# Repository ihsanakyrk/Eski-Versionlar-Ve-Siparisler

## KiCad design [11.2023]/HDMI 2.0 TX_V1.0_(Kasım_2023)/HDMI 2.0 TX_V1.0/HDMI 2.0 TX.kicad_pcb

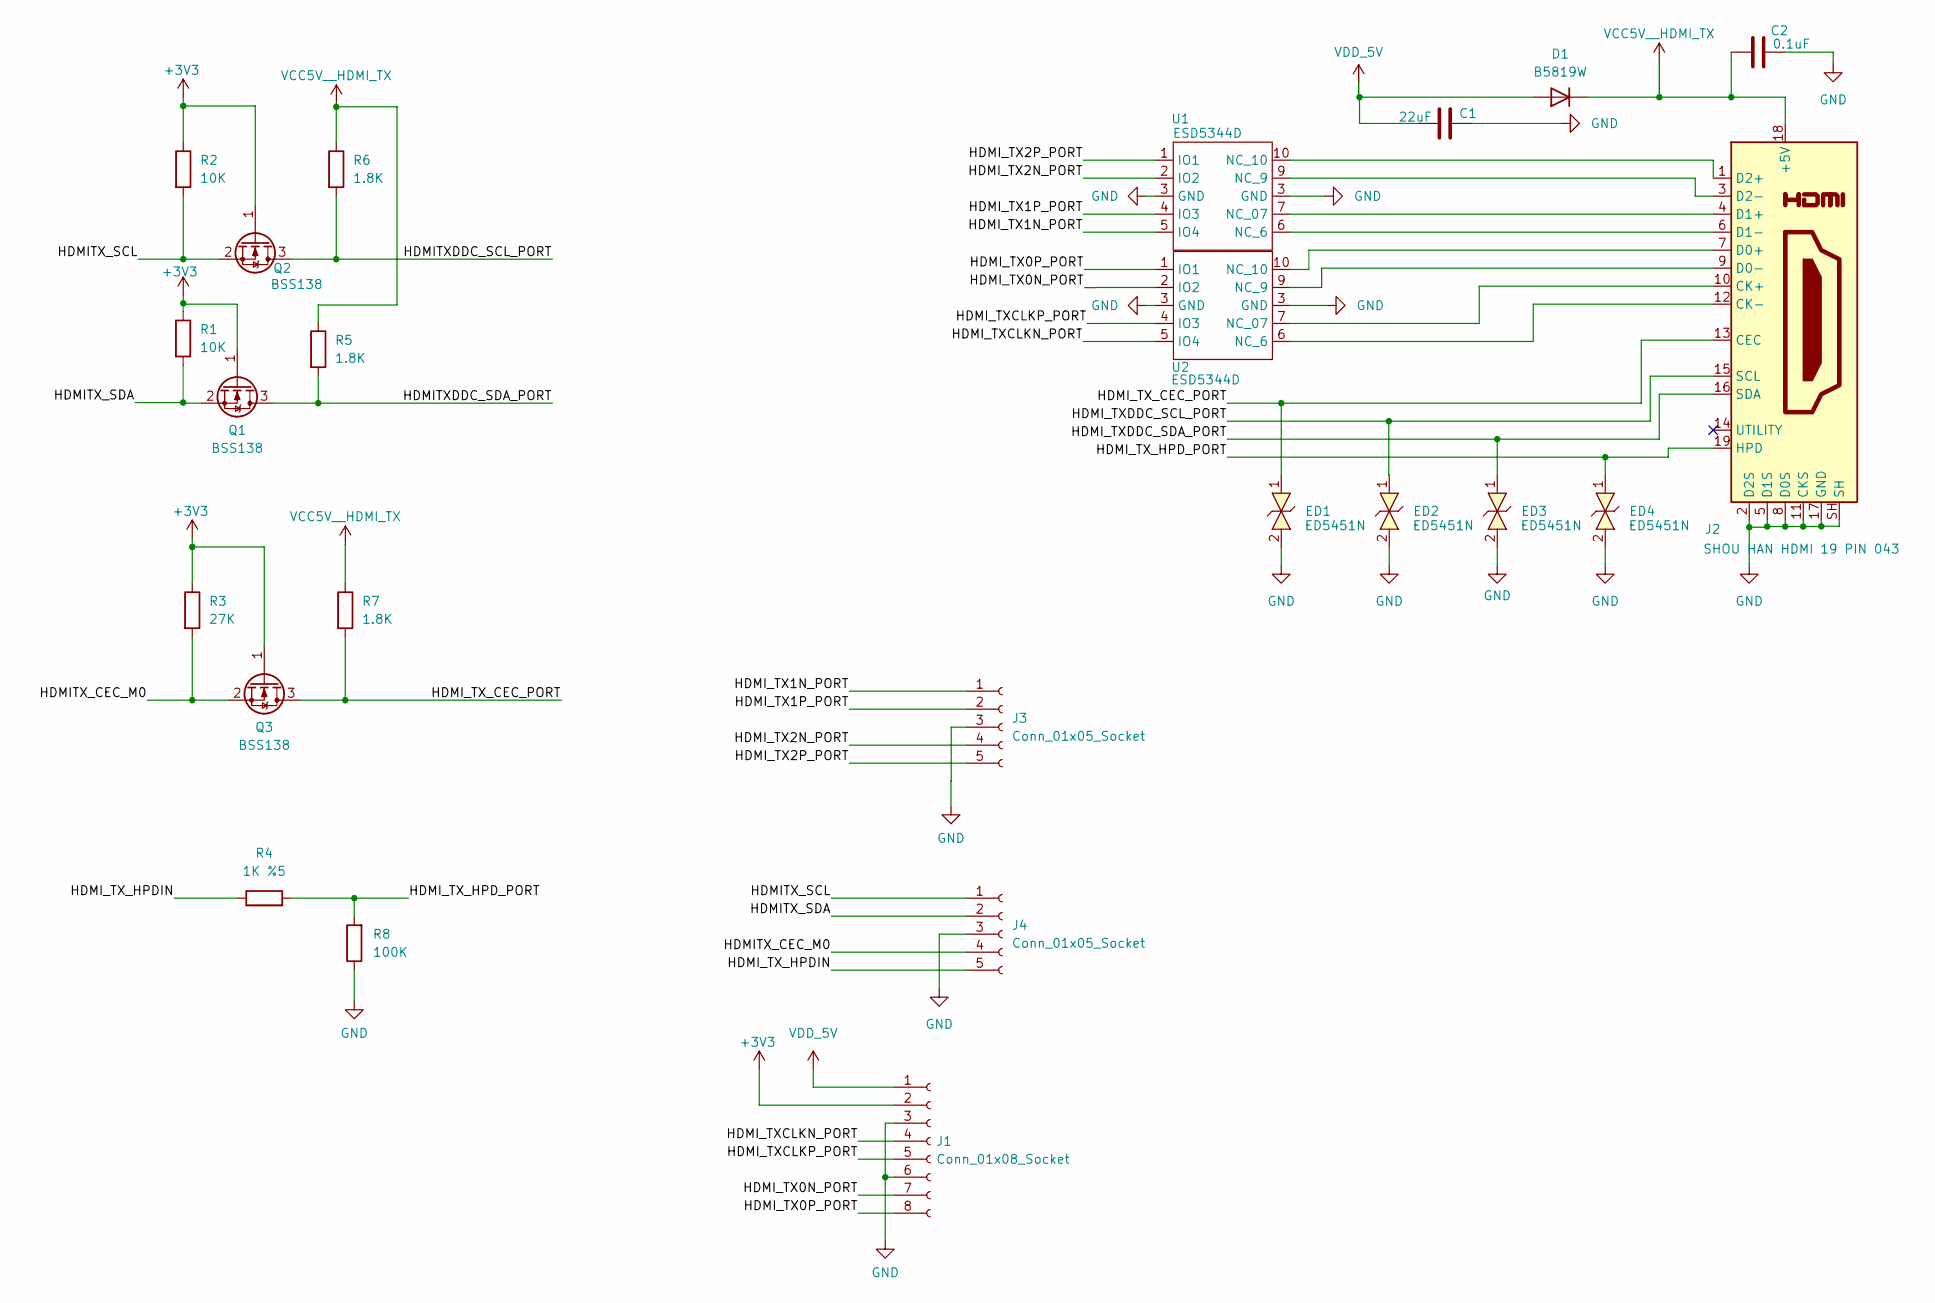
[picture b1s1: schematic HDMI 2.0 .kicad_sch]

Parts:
C1: 22uF; C_0402_1005Metric
C2: 0.1uF; C_0402_1005Metric
D1: B5819W
ED1, ED2, ED3, ED4: ED5451N; ESD5451N
J1: Conn_01x08_Socket; castelled 8
J2: SHOU HAN HDMI 19 PIN 043; HDMI 19PIN
J3, J4: Conn_01x05_Socket; Castelled 5
Q1, Q2, Q3: BSS138; SOT-23
R1, R2: 10K; R_0402_1005Metric
R3: 27K; R_0402_1005Metric
R4: 1K %5; R_0402_1005Metric
R5, R6, R7: 1.8K; R_0402_1005Metric
R8: 100K; R_0402_1005Metric
U1, U2: ESD5344D

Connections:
+3V3: J1.2, Q1.1 (G), Q2.1 (G), Q3.1 (G), R1.1, R2.1, R3.1
/HDMI 2.0 /HDMITXDDC_SCL_PORT: Q2.3 (D), R6.2
/HDMI 2.0 /HDMITXDDC_SDA_PORT: Q1.3 (D), R5.2
/HDMI 2.0 /HDMITX_CEC_M0: J4.4, Q3.2 (S), R3.2
/HDMI 2.0 /HDMITX_SCL: J4.1, Q2.2 (S), R2.2
/HDMI 2.0 /HDMITX_SDA: J4.2, Q1.2 (S), R1.2
/HDMI 2.0 /HDMI_TX0N_PORT: J1.7, U2.2 (IO2)
/HDMI 2.0 /HDMI_TX0P_PORT: J1.8, U2.1 (IO1)
/HDMI 2.0 /HDMI_TX1N_PORT: J3.1, U1.5 (IO4)
/HDMI 2.0 /HDMI_TX1P_PORT: J3.2, U1.4 (IO3)
/HDMI 2.0 /HDMI_TX2N_PORT: J3.4, U1.2 (IO2)
/HDMI 2.0 /HDMI_TX2P_PORT: J3.5, U1.1 (IO1)
/HDMI 2.0 /HDMI_TXCLKN_PORT: J1.4, U2.5 (IO4)
/HDMI 2.0 /HDMI_TXCLKP_PORT: J1.5, U2.4 (IO3)
/HDMI 2.0 /HDMI_TXDDC_SCL_PORT: ED2.1, J2.15 (SCL)
/HDMI 2.0 /HDMI_TXDDC_SDA_PORT: ED3.1, J2.16 (SDA)
/HDMI 2.0 /HDMI_TX_CEC_PORT: ED1.1, J2.13 (CEC), Q3.3 (D), R7.2
/HDMI 2.0 /HDMI_TX_HPDIN: J4.5, R4.1
/HDMI 2.0 /HDMI_TX_HPD_PORT: ED4.1, J2.19 (HPD), R4.2, R8.2
GND: C1.2, C2.2, ED1.2, ED2.2, ED3.2, ED4.2, J1.3, J1.6, J2.2 (D2S), J2.5 (D1S), J2.8 (D0S), J2.11 (CKS), J2.17 (GND), J2.SH, J3.3, J4.3, R8.1, U1.3 (GND), U2.3 (GND)
unnamed: J2.10 (CK+), U2.7 (NC_07)
unnamed: J2.12 (CK-), U2.6 (NC_6)
unnamed: J2.7 (D0+), U2.10 (NC_10)
unnamed: J2.9 (D0-), U2.9 (NC_9)
unnamed: J2.4 (D1+), U1.7 (NC_07)
unnamed: J2.6 (D1-), U1.6 (NC_6)
unnamed: J2.1 (D2+), U1.10 (NC_10)
unnamed: J2.3 (D2-), U1.9 (NC_9)
VCC5V__HDMI_TX: C2.1, D1.1 (K), J2.18 (+5V), R5.1, R6.1, R7.1
VDD_5V: C1.1, D1.2 (A), J1.1

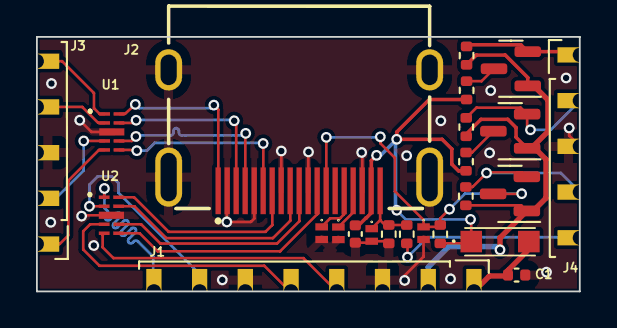
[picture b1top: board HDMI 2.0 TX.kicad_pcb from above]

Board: 2 copper layers, 30.2 x 14.1 mm, 24 parts (0 on the bottom side), 30 nets.

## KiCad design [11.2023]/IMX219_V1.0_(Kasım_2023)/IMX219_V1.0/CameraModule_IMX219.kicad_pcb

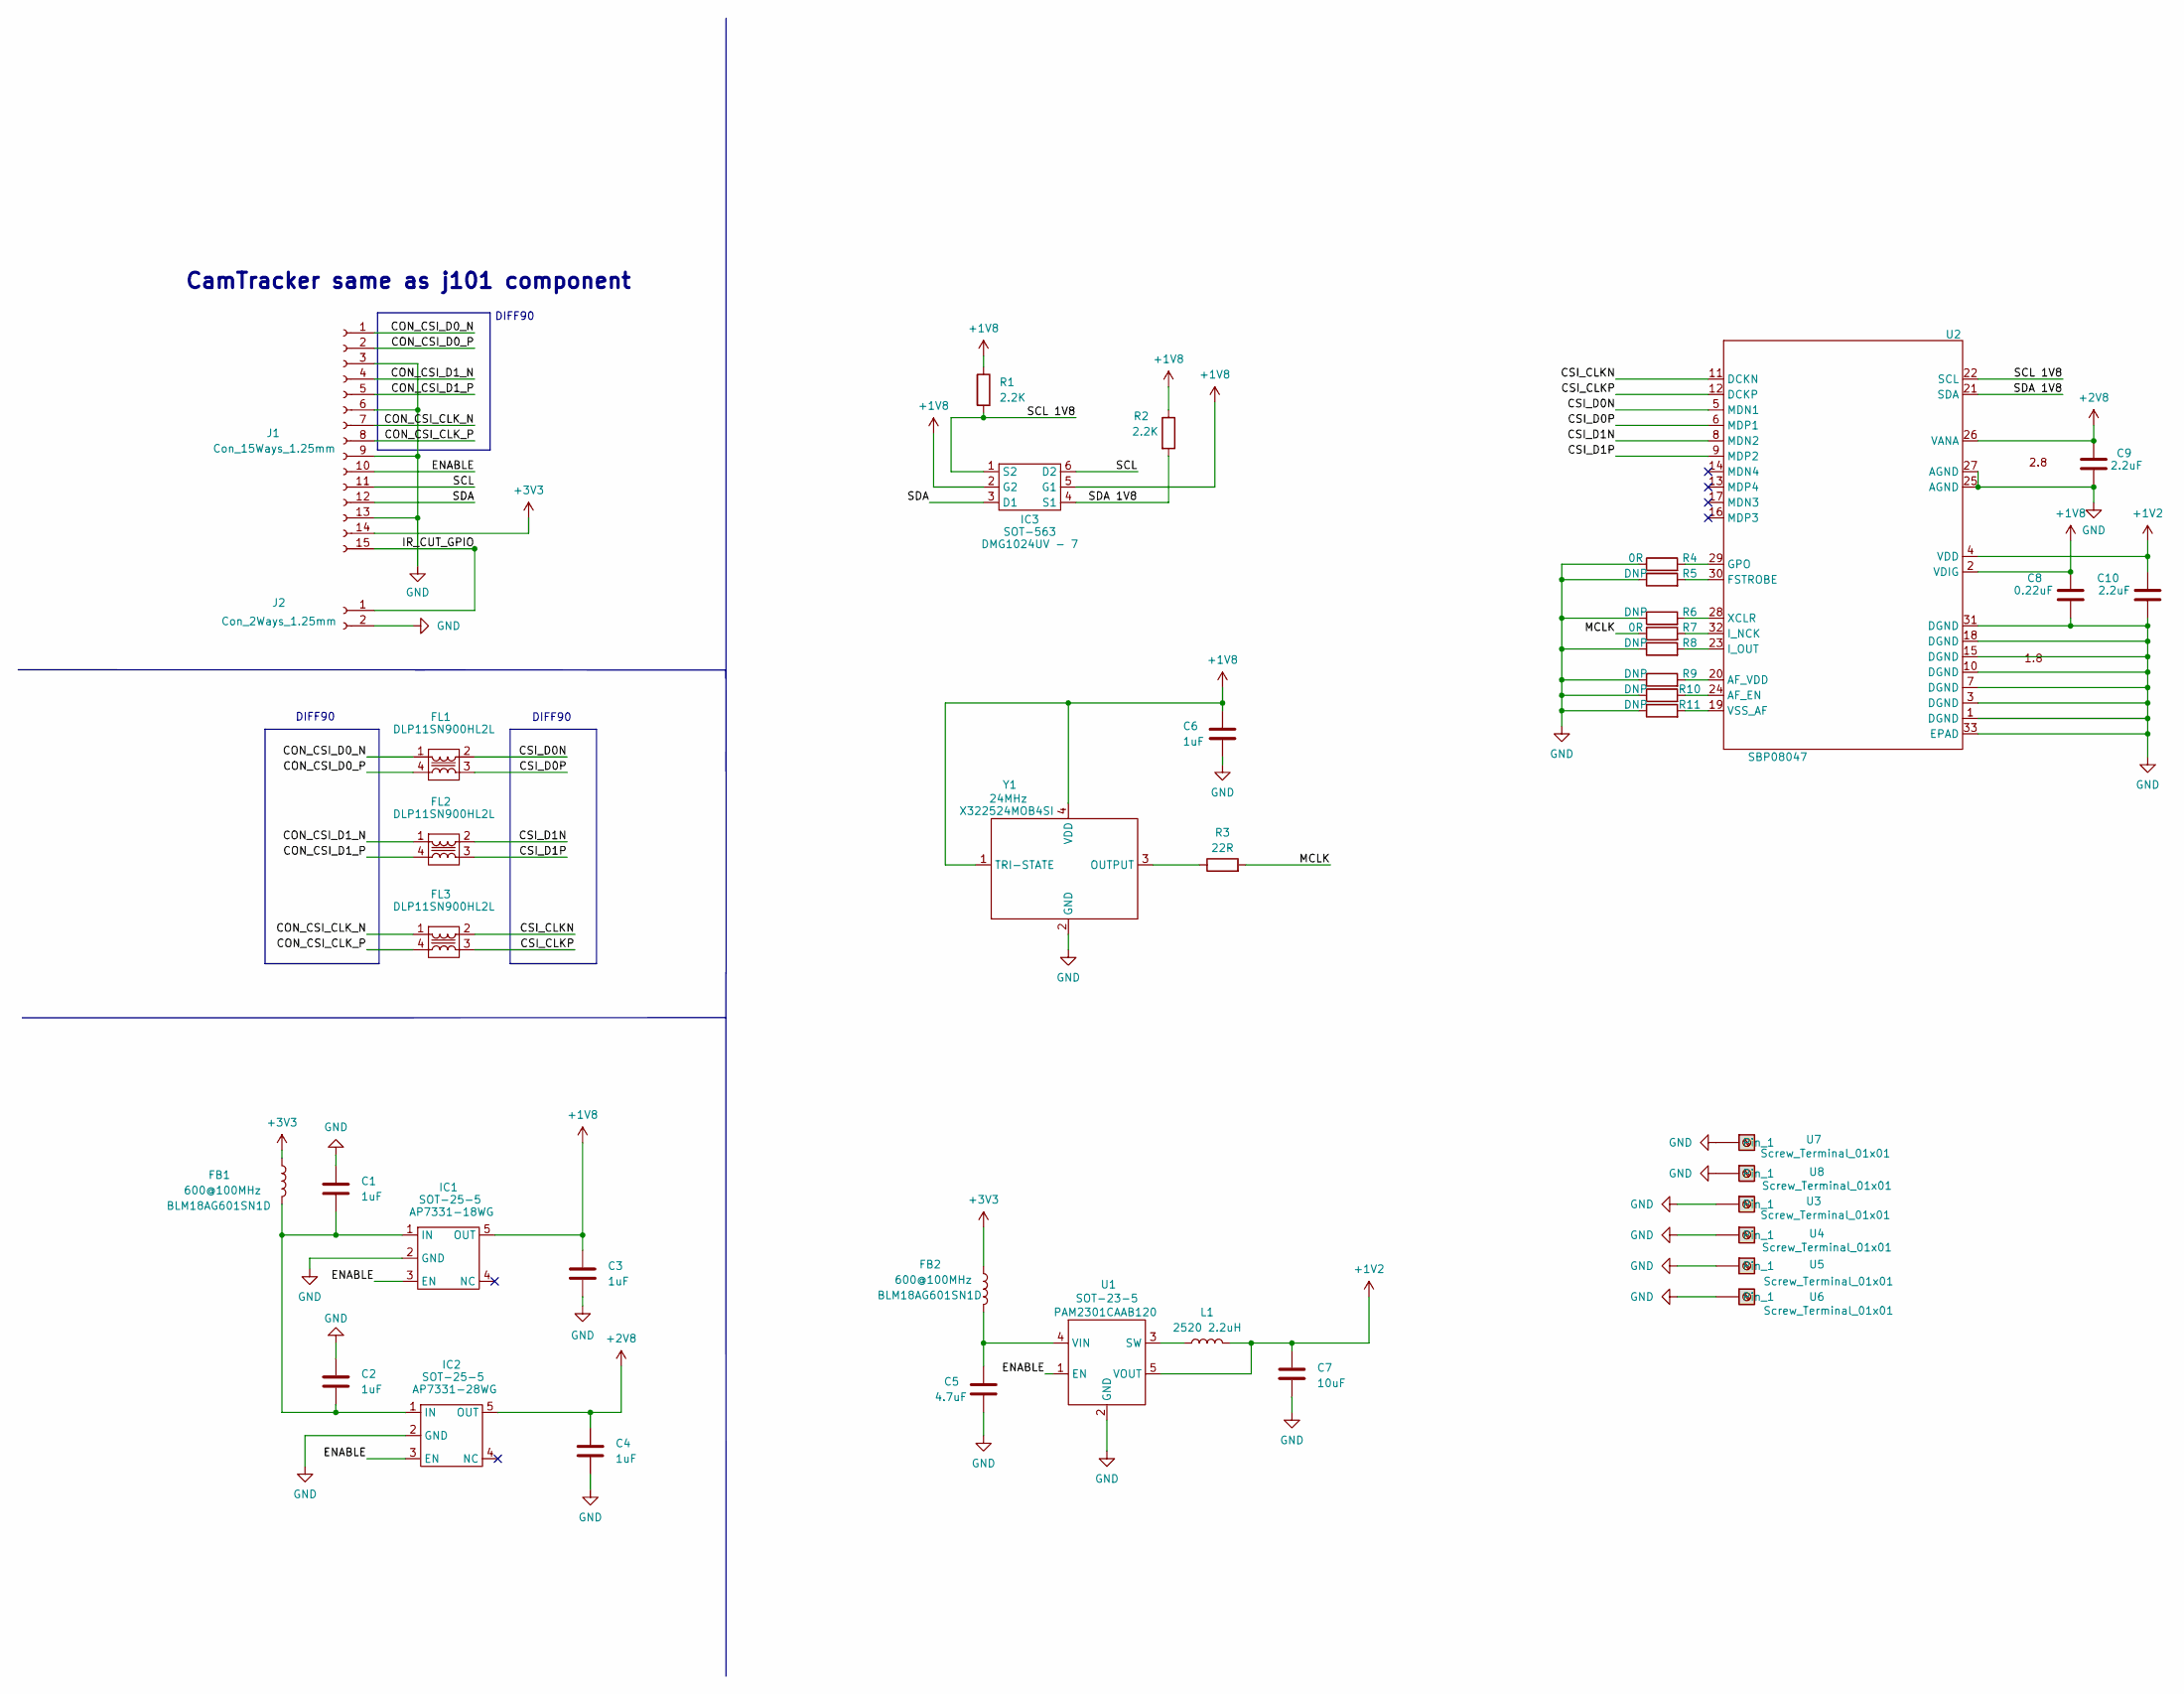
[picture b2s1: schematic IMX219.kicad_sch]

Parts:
C1, C2, C3, C4, C6: 1uF; C_0402_1005Metric
C5: 4.7uF; C_0603_1608Metric
C7: 10uF; C_0805_2012Metric
C8: 0.22uF; C_0402_1005Metric
C9, C10: 2.2uF; C_0402_1005Metric
FB1, FB2: 600@100MHz; BLM18SP221SN1B; MPN BLM18AG601SN1D
FL1, FL2, FL3: DLP11SN900HL2L; MPN DLP11SN900HL2L
IC1: SOT-25-5; AP7331; MPN AP7331-18WG
IC2: SOT-25-5; AP7331; MPN AP7331-28WG
IC3: SOT-563; MPN DMG1024UV - 7
J1: Con_15Ways_1.25mm; JST_1x15-1MP_P1.25mm_Horizontal
J2: Con_2Ways_1.25mm
L1: 2520 2.2uH; L_1008_2520Metric; MPN IFSC1008ABER2R2M01
R1, R2: 2.2K; R_0402_1005Metric
R3: 22R; R_0402_1005Metric
R4, R7: 0R; R_0402_1005Metric
R5, R6, R8, R9, R10, R11: DNP; R_0402_1005Metric
U1: SOT-23-5; MPN PAM2301CAAB120
U2: SBP08047; MPN SBP08047
U3, U4, U5, U6, U7, U8: Screw_Terminal_01x01
Y1: 24MHz; X322524MOB4SI; MPN X322524MOB4SI

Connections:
+1V2: C7.1, C10.2, L1.2, U1.5 (VOUT), U2.4 (VDD)
+1V8: C3.1, C6.1, C8.2, IC1.5 (OUT), IC3.2 (G2), IC3.5 (G1), R1.1, R2.1, U2.2 (VDIG), Y1.1 (TRI-STATE), Y1.4 (VDD)
+2V8: C4.1, C9.2, IC2.5 (OUT), U2.26 (VANA)
+3V3: FB1.1, FB2.1, J1.14
/IMX219/CON_CSI_CLK_N: FL3.1, J1.7
/IMX219/CON_CSI_CLK_P: FL3.4, J1.8
/IMX219/CON_CSI_D0_N: FL1.1, J1.1
/IMX219/CON_CSI_D0_P: FL1.4, J1.2
/IMX219/CON_CSI_D1_N: FL2.1, J1.4
/IMX219/CON_CSI_D1_P: FL2.4, J1.5
/IMX219/CSI_CLKN: FL3.2, U2.11 (DCKN)
/IMX219/CSI_CLKP: FL3.3, U2.12 (DCKP)
/IMX219/CSI_D0N: FL1.2, U2.5 (MDN1)
/IMX219/CSI_D0P: FL1.3, U2.6 (MDP1)
/IMX219/CSI_D1N: FL2.2, U2.8 (MDN2)
/IMX219/CSI_D1P: FL2.3, U2.9 (MDP2)
/IMX219/ENABLE: IC1.3 (EN), IC2.3 (EN), J1.10, U1.1 (EN)
/IMX219/IR_CUT_GPIO: J1.15, J2.1
/IMX219/MCLK: R3.2, R7.1
/IMX219/SCL: IC3.6 (D2), J1.11
/IMX219/SCL 1V8: IC3.1 (S2), R1.2, U2.22 (SCL)
/IMX219/SDA: IC3.3 (D1), J1.12
/IMX219/SDA 1V8: IC3.4 (S1), R2.2, U2.21 (SDA)
GND: C1.1, C2.1, C3.2, C4.2, C5.2, C6.2, C7.2, C8.1, C9.1, C10.1, IC1.2 (GND), IC2.2 (GND), J1.3, J1.6, J1.9, J1.13, J2.2, R4.1, R5.1, R6.1, R8.1, R9.1, R10.1, R11.1, U1.2 (GND), U2.1 (DGND), U2.3 (DGND), U2.7 (DGND), U2.10 (DGND), U2.15 (DGND), U2.18 (DGND), U2.25 (AGND), U2.27 (AGND), U2.31 (DGND), U2.33 (EPAD), U3., U4., U5., U6., U7., U8., Y1.2 (GND)
unnamed: C1.2, C2.2, FB1.2, IC1.1 (IN), IC2.1 (IN)
unnamed: L1.1, U1.3 (SW)
unnamed: C5.1, FB2.2, U1.4 (VIN)
unnamed: R10.2, U2.24 (AF_EN)
unnamed: R9.2, U2.20 (AF_VDD)
unnamed: R5.2, U2.30 (FSTROBE)
unnamed: R4.2, U2.29 (GPO)
unnamed: R7.2, U2.32 (I_NCK)
unnamed: R8.2, U2.23 (I_OUT)
unnamed: R11.2, U2.19 (VSS_AF)
unnamed: R6.2, U2.28 (XCLR)
unnamed: R3.1, Y1.3 (OUTPUT)

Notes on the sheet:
DIFF90
CamTracker same as j101 component

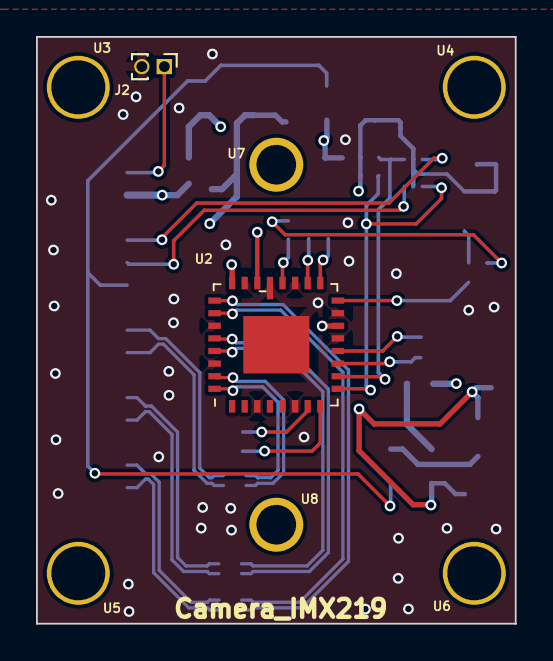
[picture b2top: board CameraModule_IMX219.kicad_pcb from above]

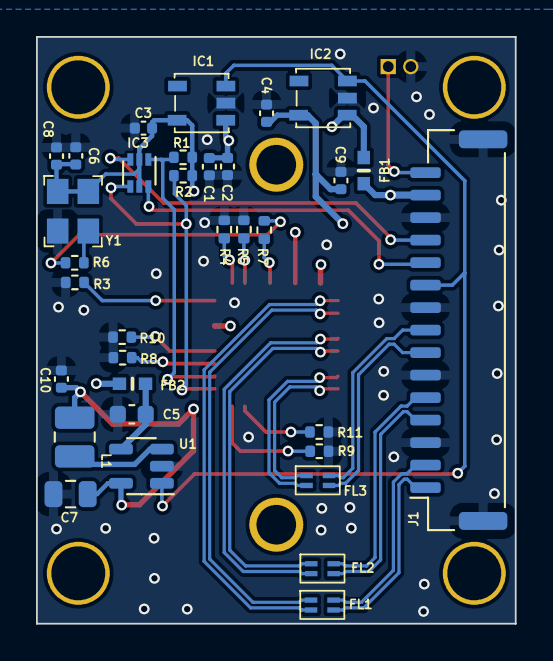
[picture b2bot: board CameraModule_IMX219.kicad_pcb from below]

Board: 4 copper layers, 26.6 x 32.6 mm, 41 parts (33 on the bottom side), 36 nets.

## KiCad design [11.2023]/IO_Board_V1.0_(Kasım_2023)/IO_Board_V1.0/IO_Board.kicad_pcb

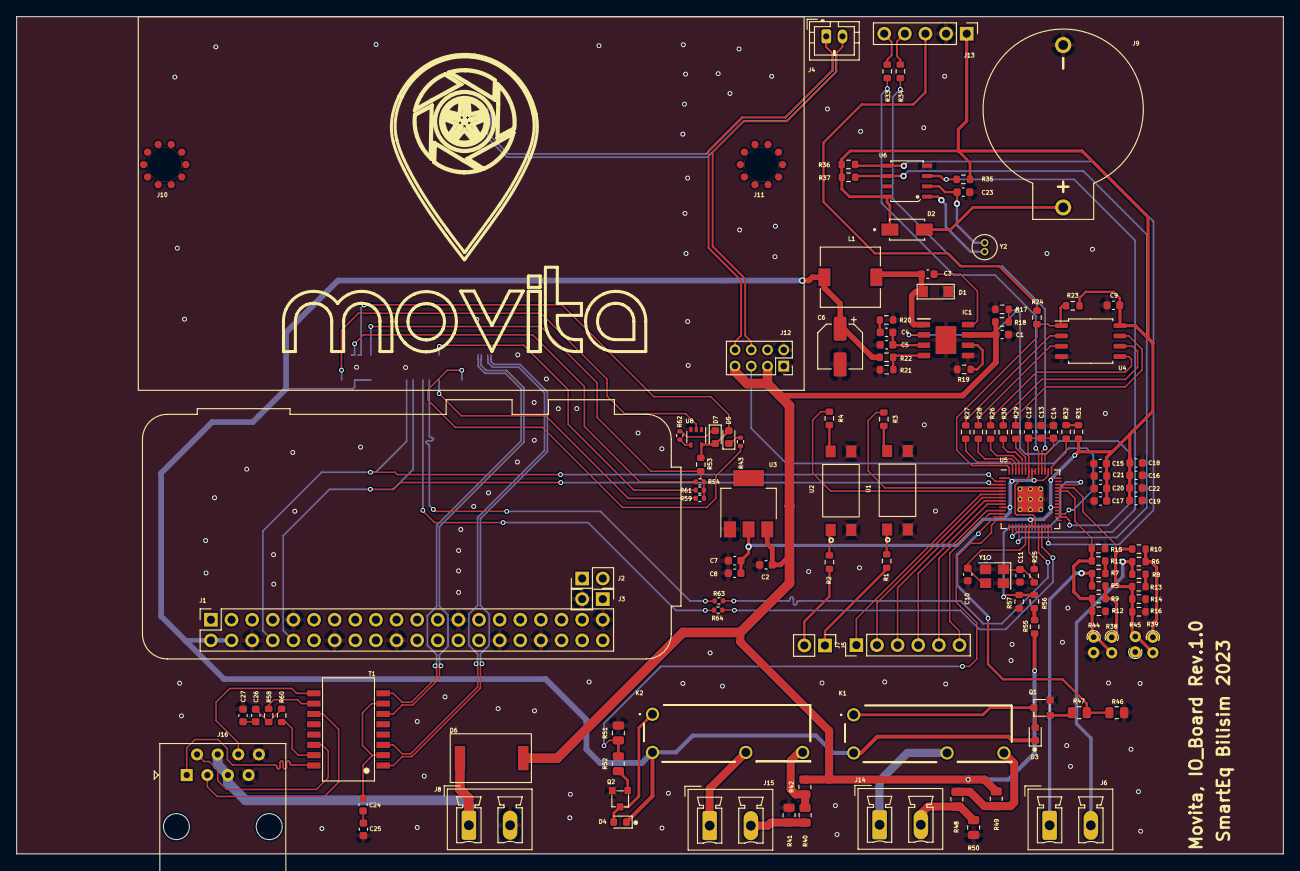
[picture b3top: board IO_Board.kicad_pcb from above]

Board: 2 copper layers, 156.0 x 103.1 mm, 131 parts (1 on the bottom side), 109 nets.

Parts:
C1, C2: 10uF; C_0603_1608Metric
C3, C12, C13, C16, C17, C18, C19, C20, C21, C22: 100nF; C_0603_1608Metric
C4: 150pF; C_0603_1608Metric
C5: DNP; C_0603_1608Metric
C6: 100uF; CP_Elec_5x5.4
C7: 22uF; C_0603_1608Metric
C8: 0.1uF; C_0603_1608Metric
C9: 1nF; C_0603_1608Metric
C10, C11: 27pF; C_0603_1608Metric
C14, C15: 1uF; C_0603_1608Metric
C23: 22pF; C_0603_1608Metric
C24, C25: 0.01uF; C_0603_1608Metric
C26, C27: 1000pF; C_0603_1608Metric
D1: SS34FA
D2: SS14; DIOM4325X250N
D3, D4: MRA4007T3G
D5: LED Green; LED_0603_1608Metric
D6: S6MC
D7: LED Red; LED_0603_1608Metric
IC1: MP1584EN; MP1584
J1: FEMALE Through Hole Pin Header; PinHeader_2x20_P2.54mm_Vertical
J2, J3: DNP; PinHeader_1x02_P2.54mm_Vertical
J4: JST_PH_B2B-PH-K_1x02_P2.00mm_Vertical
J5: FEMALE Through Hole Pin Header; PinHeader_1x02_P2.54mm_Vertical
J6, J8, J14, J15: KF2EDGR-Y-5.08-2P-Right Angle
J7: DNP; PinHeader_1x06_P2.54mm_Vertical
J9: MYOUNG BS-02-A1AJ010
J10, J11: M3x*0.5 L=8; Screw_terminal_shinbo
J12: FEMALE Through Hole Pin Header; PinSocket_2x04_P2.00mm_Vertical
J13: FEMALE Through Hole Pin Header; PinHeader_1x05_P2.54mm_Vertical
J16: RJ45; RJ45_Amphenol_54602-x08_Horizontal
K1, K2: DNP; HF46F_5-HS1
L1: 10uH; L_7.3x7.3_H3.5
Q1, Q2: MMBT2222ALT1G
R1, R2, R3, R4, R25: 1K; R_0603_1608Metric
R5, R6, R53: 0R; R_0603_1608Metric
R7, R8, R23, R55: DNP; R_0603_1608Metric
R9, R10, R15, R16: 100R; R_0603_1608Metric
R11, R13: 1.78K; R_0603_1608Metric
R12, R14: 220R; R_0603_1608Metric
R17: 2.2K; R_0603_1608Metric
R18, R19, R20: 100K; R_0603_1608Metric
R21: 40.2K; R_0603_1608Metric
R22: 210K; R_0603_1608Metric
R24: 10K; R_0603_1608Metric
R26, R27, R28, R29, R30, R33, R34: 27R; R_0603_1608Metric
R31: 200R; R_0603_1608Metric
R32: 1R; R_0603_1608Metric
R35: 4.7K; R_0603_1608Metric
R36, R37: 4.7K %5; R_0603_1608Metric
R38, R39, R44, R45: DNP; R_Axial_DIN0204_L3.6mm_D1.6mm_P1.90mm_Vertical
R40, R48: DNP; R_0805_2012Metric
R41, R42, R49, R50: 0R; R_0805_2012Metric
R43, R62: 1K; R_0402_1005Metric
R46, R51: 10K; R_0805_2012Metric
R47, R52: 1K; R_0805_2012Metric
R54, R63, R64: DNP; R_0402_1005Metric
R56: 725R; R_0603_1608Metric
R57: 275R; R_0603_1608Metric
R58, R60: 75R; R_0603_1608Metric
R59, R61: 2.2K 1%; R_0402_1005Metric
T1: H1102NL
U1, U2: PC817C_4PIN_SMD; PC817C SMD 4pin
U3: LM1117S-3.3; SOT-223
U4: W25Q128JVSIQ; W25Q128JVS
U5: RP2040; RP20400
U6: PCF8563
U7: DNP; Raspberry-Pi-4-Compute-Module
U8: 74LVC1G07SE-7; SOT-353_SC-70-5
Y1: TAXM12M4RLBDDT2T
Y2: ECS-3X8X

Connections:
3.3V: C7.1, C8.1, C9.1, C15.1, C16.1, C17.1, C18.1, C19.1, C20.1, C21.1, C22.1, D2.C, J13.1, R23.1, R31.1, R35.2, R36.2, R37.2, U3.2 (VO), U4.8 (VCC), U5.1 (IOVDD), U5.10 (IOVDD), U5.22 (IOVDD), U5.33 (IOVDD), U5.42 (IOVDD), U5.44 (VREG_IN), U5.48 (USB_VDD), U5.49 (IOVDD), U6.8 (VDD)
5V: C6.1, D3.1 (K), D4.1 (K), J1.2, J1.4, K1.2 (COIL_2), K2.2 (COIL_2), L1.2, R22.2, U7.77 (+5v_(Input)), U7.79 (+5v_(Input)), U7.81 (+5v_(Input)), U7.83 (+5v_(Input)), U7.85 (+5v_(Input)), U7.87 (+5v_(Input))
+1V1: C12.1, C13.1, C14.1, U5.23 (DVDD), U5.45 (VREG_VOUT), U5.50 (DVDD)
/CM4_GPIO/+1.8V: R54.1, U7.88 (+1.8v_(Output)), U7.90 (+1.8v_(Output))
/CM4_GPIO/+3.3v: D5.2 (A), D7.2 (A), R53.2, U7.84 (+3.3v_(Output)), U7.86 (+3.3v_(Output)), U8.5 (VCC)
/CM4_GPIO/CM4_SWCLK: R63.2, U5.24 (SWCLK)
/CM4_GPIO/CM4_SWDIO: R64.2, U5.25 (SWD)
/CM4_GPIO/GPIO_VREF: R53.1, R54.2, R59.1, R61.1, U7.78 (GPIO_VREF(1.8v/3.3v_Input))
/CM4_GPIO/ID_SC: R59.2, U7.35 (ID_SC)
/CM4_GPIO/ID_SD: R61.2, U7.36 (ID_SD)
/CM4_GPIO/USB2_N: J4.1, J12.8, U7.103 (USB2_N)
/CM4_GPIO/USB2_P: J4.2, J12.6, U7.105 (USB2_P)
/CM4_GPIO/VOUT_CAM: D6.2 (A), J8.1, J16.4, J16.5
/CM4_GPIO/nPWR_LED: U7.95 (nPI_LED_PWR), U8.2
/Connectors/Analog_Input1: J6.1, R5.2, R7.2
/Connectors/Analog_Input2: J6.2, R6.2, R8.2
/Connectors/GP4: J7.1, U5.6 (GPIO4)
/Connectors/GP5: J7.2, U5.7 (GPIO5)
/Connectors/GP6: J7.3, U5.8 (GPIO6)
/Connectors/GP7: J7.4, U5.9 (GPIO7)
/Connectors/GP8: J7.5, U5.11 (GPIO8)
/Connectors/GP9: J7.6, U5.12 (GPIO9)
/Connectors/GP26_AO: R9.1, R11.1, R12.1, R15.2, R38.2, R44.1, U5.38 (GPIO26_ADC0)
/Connectors/GP27_AO: R10.1, R13.1, R14.1, R16.2, R39.2, R45.2, U5.39 (GPIO27_ADC1)
/Connectors/GP28_AO: R56.1, R57.1, U5.40 (GPIO28_ADC2)
/Connectors/GP_2: R3.1, U5.4 (GPIO2)
/Connectors/GP_3: R4.1, U5.5 (GPIO3)
/GSM/EN_3.8V: J12.5, U5.31 (GPIO20)
/POWER/EN: IC1.2 (EN), R17.1, R18.2, U5.30 (GPIO19)
/POWER/RTCL 3V3: D2.A, J9.1 (+)
/RP2040/I2C3_SCL_M0: R37.1, U5.18 (GPIO15), U6.6 (SCL)
/RP2040/I2C3_SDA_M0: R36.1, U5.27 (GPIO16), U6.5 (SDA)
/RP2040/QSPI_CSN: R23.2, R24.1, U4.1 (~CS~{}), U5.56 (QSPI_SS)
/RP2040/QSPI_SCLK: R30.2, U4.6 (CLK)
/RP2040/QSPI_SD0: R26.2, U4.5 (DI(IO0))
/RP2040/QSPI_SD1: R27.2, U4.2 (DO(IO1))
/RP2040/QSPI_SD2: R28.2, U4.3 (~WP~{}(IO2))
/RP2040/QSPI_SD3: R29.2, U4.7 (~HOLD~{}/~RESET/~IO3)
/RP2040/RTCIC_INT_L: R35.1, U5.16 (GPIO13), U6.3 (INT)
/RP2040/Relay1_EN: R46.1, R47.2, U5.13 (GPIO10)
/RP2040/Relay2_EN: R51.1, R52.2, U5.14 (GPIO11)
/RP2040/USB D N: J13.4, R34.1
/RP2040/USB D P: J13.5, R33.1
/RP2040/XIN: C10.1, U5.20 (XIN), Y1.3
/RP2040/XOUT: R25.1, U5.21 (XOUT)
/Raspberry Pi Zero/GPIO14: J1.8, U5.2 (GPIO0), U7.55 (GPIO14)
/Raspberry Pi Zero/GPIO15: J1.10, U5.3 (GPIO1), U7.51 (GPIO15)
/Relay/relay output 1: J14.1, K1.3 (NO)
/Relay/relay output 2: J15.1, K2.3 (NO)
ADC_VREF: R31.2, R32.1
GND: C1.2, C2.2, C5.2, C6.2, C7.2, C8.2, C9.2, C10.2, C11.2, C12.2, C13.2, C14.2, C15.2, C16.2, C17.2, C18.2, C19.2, C20.2, C21.2, C22.2, C23.2, C25.2, C27.2, D1.2 (A), IC1.5 (GND), IC1.9 (EP), J1.6, J1.9, J1.14, J1.20, J1.25, J1.30, J1.34, J1.39, J3.2, J8.2, J9.2 (-), J12.1, J12.2, J13.2, J16.7, J16.8, Q1.2 (E), Q2.2 (E), R12.2, R14.2, R15.1, R16.1, R17.2, R19.2, R20.2, R21.2, R41.1, R44.2, R45.1, R46.2, R50.1, R51.2, R57.2, U1.2 (K), U1.3 (E), U2.2 (K), U2.3 (E), U3.1 (ADJ), U4.4 (GND), U5.19 (TESTEN), U5.57 (GND), U6.4 (VSS), U7.1 (GND), U7.2 (GND), U7.7 (GND), U7.8 (GND), U7.13 (GND), U7.14 (GND), U7.22 (GND), U7.23 (GND), U7.32 (GND), U7.33 (GND), U7.42 (GND), U7.43 (GND), U7.52 (GND), U7.53 (GND), U7.59 (GND), U7.60 (GND), U7.65 (GND), U7.66 (GND), U7.71 (GND), U7.74 (GND), U7.98 (GND), U7.107 (GND), U7.108 (GND), U7.113 (GND), U7.114 (GND), U7.119 (GND), U7.120 (GND), U7.125 (GND), U7.126 (GND), U7.131 (GND), U7.132 (GND), U7.137 (GND), U7.138 (GND), U7.144 (GND), U7.150 (GND), U7.155 (GND), U7.156 (GND), U7.161 (GND), U7.162 (GND), U7.167 (GND), U7.168 (GND), U7.173 (GND), U7.174 (GND), U7.179 (GND), U7.180 (GND), U7.185 (GND), U7.186 (GND), U7.191 (GND), U7.192 (GND), U7.197 (GND), U7.198 (GND), U8.3 (GND), Y1.2, Y1.4
unnamed: C4.2, R20.1
unnamed: C11.1, R25.2, Y1.1
unnamed: C24.2, C25.1
unnamed: C26.1, R58.1, R60.1
unnamed: C26.2, C27.1
unnamed: C3.2, D1.1 (K), IC1.1 (SW), L1.1
unnamed: D3.2 (A), K1.1 (COIL_1), Q1.3 (C)
unnamed: D4.2 (A), K2.1 (COIL_1), Q2.3 (C)
unnamed: D5.1 (K), R43.1
unnamed: D7.1 (K), R62.1
unnamed: C3.1, IC1.8 (BST)
unnamed: C4.1, C5.1, IC1.3 (COMP)
unnamed: IC1.4 (FB), R21.1, R22.1
unnamed: IC1.6 (FREQ), R19.1
unnamed: J5.1, R1.1
unnamed: J5.2, R2.1
unnamed: J13.3, R24.2
unnamed: J14.2, R48.1, R50.2
unnamed: J15.2, R40.2, R41.2
unnamed: K1.4 (COM), R48.2, R49.2
unnamed: K2.4 (COM), R40.1, R42.1
unnamed: Q1.1 (B), R47.1
unnamed: Q2.1 (B), R52.1
unnamed: R6.1, R10.2, R39.1
unnamed: R7.1, R11.2
unnamed: R8.1, R13.2
unnamed: R5.1, R9.2, R38.1
unnamed: R55.2, R56.2
unnamed: R62.2, U8.4
unnamed: C24.1, T1.2 (CT1), T1.7 (CT2)
unnamed: R58.2, T1.10 (CT3)
unnamed: R60.2, T1.15 (CT4)
unnamed: R1.2, U1.1 (A)
unnamed: R3.2, U1.4 (C)
unnamed: R2.2, U2.1 (A)
unnamed: R4.2, U2.4 (C)
unnamed: R32.2, U5.43 (ADC_AVDD)
unnamed: R30.1, U5.52 (QSPI_SCLK)
unnamed: R26.1, U5.53 (QSPI_SD0)
unnamed: R27.1, U5.55 (QSPI_SD1)
unnamed: R28.1, U5.54 (QSPI_SD2)
unnamed: R29.1, U5.51 (QSPI_SD3)
unnamed: R34.2, U5.46 (USB_DM)
unnamed: R33.2, U5.47 (USB_DP)
unnamed: U6.1 (OSCI), Y2.1
unnamed: C23.1, U6.2 (OSCO), Y2.2
unnamed: R64.1, U7.45 (GPIO24)
unnamed: R63.1, U7.41 (GPIO25)
unnamed: R43.2, U7.21 (PI_nLED_Activity)
RX_N: T1.8 (RD-), U7.12 (Ethernet_Pair0_P)
RX_P: T1.6 (RD+), U7.10 (Ethernet_Pair0_N)
TRD0_N: J16.2, T1.14 (TX-)
TRD0_P: J16.1, T1.16 (TX+)
TRD1_N: J16.6, T1.9 (RX-)
TRD1_P: J16.3, T1.11 (RX+)
TX_N: T1.3 (TD-), U7.6 (Ethernet_Pair1_N)
TX_P: T1.1 (TD+), U7.4 (Ethernet_Pair1_P)
VIN: C1.1, C2.1, D6.1 (K), IC1.7 (VIN), J12.3, J12.7, R18.1, R42.2, R49.1, R55.1, U3.3 (VI)

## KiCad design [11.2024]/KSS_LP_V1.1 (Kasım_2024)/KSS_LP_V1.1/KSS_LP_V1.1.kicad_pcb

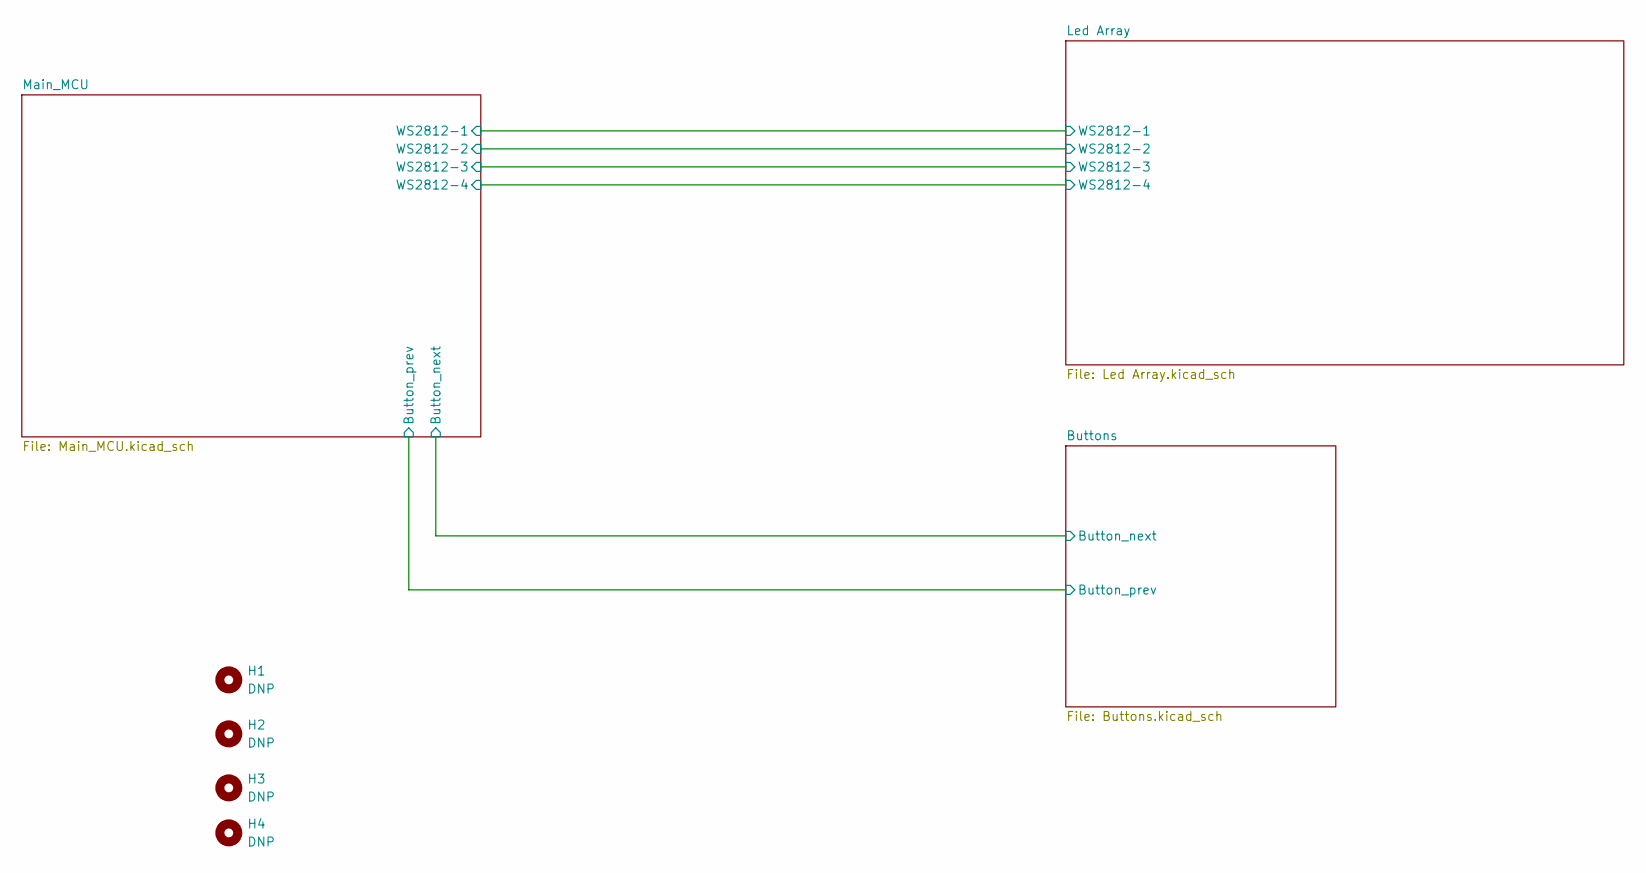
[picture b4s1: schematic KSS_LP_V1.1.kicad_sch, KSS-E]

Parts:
H1, H2, H3, H4: DNP; MountingHole_3mm

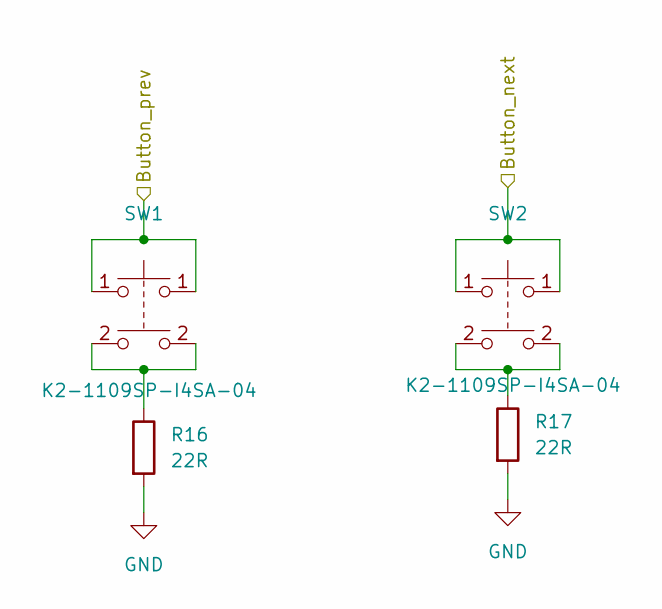
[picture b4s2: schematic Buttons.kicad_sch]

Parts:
R16, R17: 22R; R_0603_1608Metric
SW1, SW2: K2-1109SP-I4SA-04

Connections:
/Main_MCU/GPIO2: SW1.1; also elsewhere on the board
/Main_MCU/GPIO3: SW2.1; also elsewhere on the board
GND: R16.2, R17.2; also elsewhere on the board
unnamed: R16.1, SW1.2
unnamed: R17.1, SW2.2

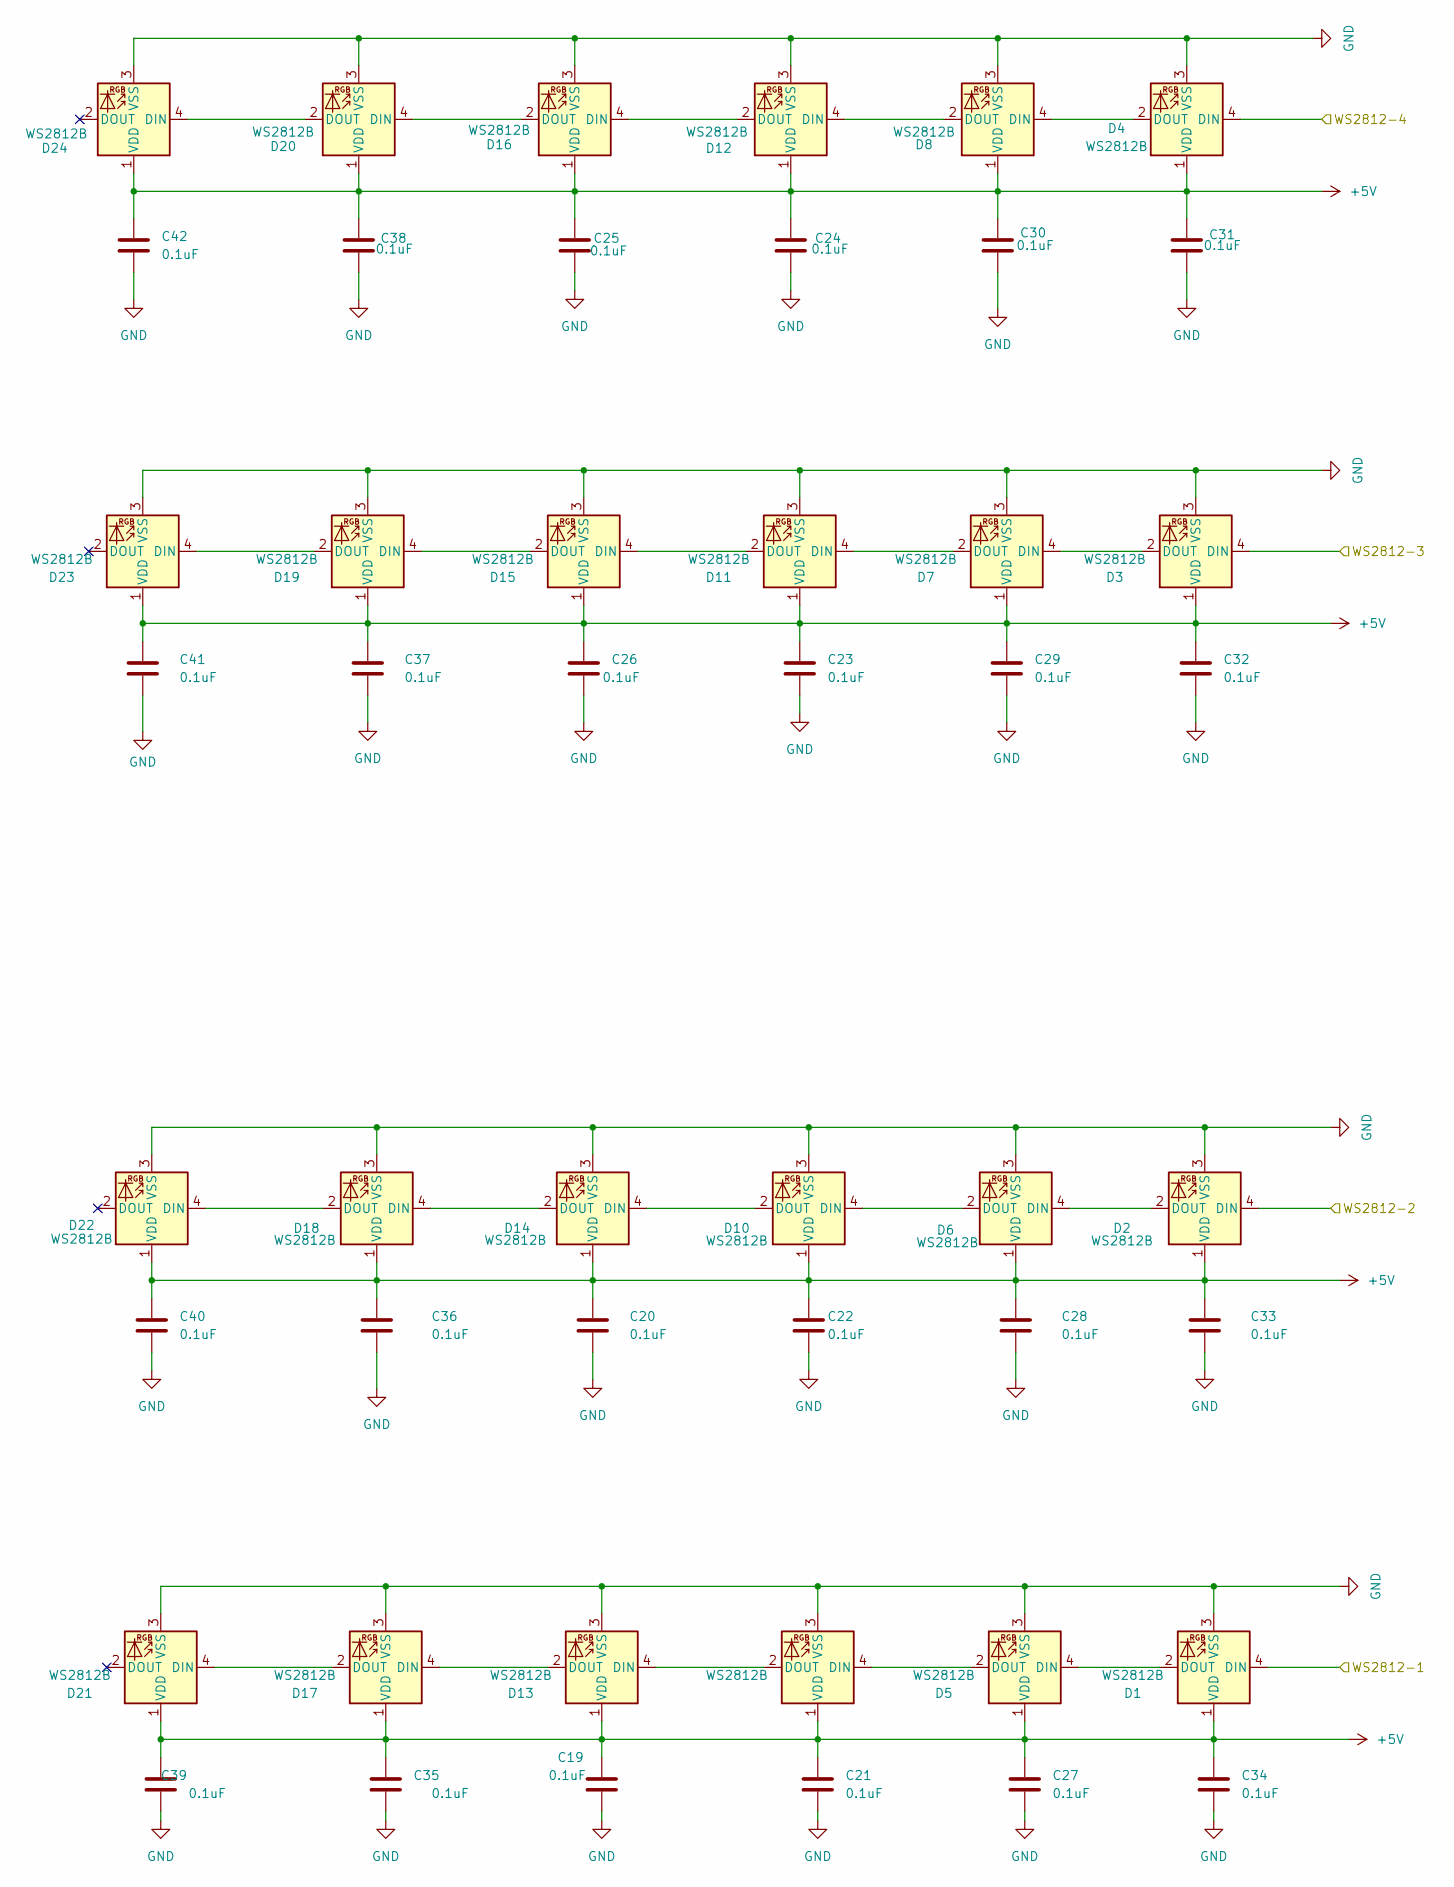
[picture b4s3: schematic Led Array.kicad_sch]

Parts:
C19, C20, C21, C22, C23, C24, C25, C26, C27, C28, C29, C30, C31, C32, C33, C34, C35, C36, C37, C38, C39, C40, C41, C42: 0.1uF; C_0603_1608Metric
D1, D2, D3, D4, D5, D6, D7, D8, D9, D10, D11, D12, D13, D14, D15, D16, D17, D18, D19, D20, D21, D22, D23, D24: WS2812B; LED_WS2812B_PLCC4_5.0x5.0mm_P3.2mm

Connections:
+5V: C19.1, C20.1, C21.1, C22.1, C23.1, C24.1, C25.1, C26.1, C27.1, C28.1, C29.1, C30.1, C31.1, C32.1, C33.1, C34.1, C35.1, C36.1, C37.1, C38.1, C39.1, C40.1, C41.1, C42.1, D1.1 (VDD), D2.1 (VDD), D3.1 (VDD), D4.1 (VDD), D5.1 (VDD), D6.1 (VDD), D7.1 (VDD), D8.1 (VDD), D9.1 (VDD), D10.1 (VDD), D11.1 (VDD), D12.1 (VDD), D13.1 (VDD), D14.1 (VDD), D15.1 (VDD), D16.1 (VDD), D17.1 (VDD), D18.1 (VDD), D19.1 (VDD), D20.1 (VDD), D21.1 (VDD), D22.1 (VDD), D23.1 (VDD), D24.1 (VDD); also elsewhere on the board
/Main_MCU/GPIO10: D4.4 (DIN); also elsewhere on the board
/Main_MCU/GPIO11: D3.4 (DIN); also elsewhere on the board
/Main_MCU/GPIO12: D2.4 (DIN); also elsewhere on the board
/Main_MCU/GPIO13: D1.4 (DIN); also elsewhere on the board
GND: C19.2, C20.2, C21.2, C22.2, C23.2, C24.2, C25.2, C26.2, C27.2, C28.2, C29.2, C30.2, C31.2, C32.2, C33.2, C34.2, C35.2, C36.2, C37.2, C38.2, C39.2, C40.2, C41.2, C42.2, D1.3 (VSS), D2.3 (VSS), D3.3 (VSS), D4.3 (VSS), D5.3 (VSS), D6.3 (VSS), D7.3 (VSS), D8.3 (VSS), D9.3 (VSS), D10.3 (VSS), D11.3 (VSS), D12.3 (VSS), D13.3 (VSS), D14.3 (VSS), D15.3 (VSS), D16.3 (VSS), D17.3 (VSS), D18.3 (VSS), D19.3 (VSS), D20.3 (VSS), D21.3 (VSS), D22.3 (VSS), D23.3 (VSS), D24.3 (VSS); also elsewhere on the board
unnamed: D1.2 (DOUT), D5.4 (DIN)
unnamed: D2.2 (DOUT), D6.4 (DIN)
unnamed: D3.2 (DOUT), D7.4 (DIN)
unnamed: D4.2 (DOUT), D8.4 (DIN)
unnamed: D5.2 (DOUT), D9.4 (DIN)
unnamed: D6.2 (DOUT), D10.4 (DIN)
unnamed: D10.2 (DOUT), D14.4 (DIN)
unnamed: D7.2 (DOUT), D11.4 (DIN)
unnamed: D11.2 (DOUT), D15.4 (DIN)
unnamed: D8.2 (DOUT), D12.4 (DIN)
unnamed: D12.2 (DOUT), D16.4 (DIN)
unnamed: D9.2 (DOUT), D13.4 (DIN)
unnamed: D13.2 (DOUT), D17.4 (DIN)
unnamed: D14.2 (DOUT), D18.4 (DIN)
unnamed: D15.2 (DOUT), D19.4 (DIN)
unnamed: D16.2 (DOUT), D20.4 (DIN)
unnamed: D17.2 (DOUT), D21.4 (DIN)
unnamed: D18.2 (DOUT), D22.4 (DIN)
unnamed: D19.2 (DOUT), D23.4 (DIN)
unnamed: D20.2 (DOUT), D24.4 (DIN)
